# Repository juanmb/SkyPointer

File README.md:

# SkyPointer

## Description

An open-hardware altazimuth mount with a laser pointer.

The following block diagram shows the current setup:

## CAD

The SkyPointer mechanical parts were designed to be easily fabricated with a 3D
printer. The `cad` folder contains the CAD files in Step, STL and
[FreeCAD](http://www.freecadweb.org) formats.

## Electronics

Circuit schematics and PCB layout were designed with [Kicad](http://kicad.org).
They are stored in the `kicad` folder.

## Arduino

An Arduino Uno board controls two stepper motors (azimuth and elevation) using
a [CNC shield](http://blog.protoneer.co.nz/arduino-cnc-shield/) with some
modifications (documentation in progress).

The Arduino firmware is located in a
[separate repo](https://github.com/davidvg/ArduinoSkyPointer).

## The Python server

The server receives "goto" messages from
[Stellarium](http://www.stellarium.org/) and sends "current position" packets back.

The Stellarium client-server protocol is documented
[here](http://www.stellarium.org/wiki/index.php/Telescope_Control_%28client-server%29).

### Installing the server in GNU/Linux

Install the required dependencies using your package manager. In Debian/Ubuntu,
you can use apt-get like this

```
$ sudo apt-get install pyqt4-dev-tools python-numpy python-scipy
```

Now you can install the *skypointer* package with pip

```
$ sudo pip install skypointer
```

Alternatively, you can clone this repo and call `setup.py` directly from the
`python` folder

```
$ git clone https://github.com/juanmb/SkyPointer.git
$ cd python
$ python setup.py install
```

For development, it is strongly recommended to install this package into a
[virtual environment](https://virtualenv.pypa.io/en/latest/).

### Installing the server in Windows

Using [Anaconda](https://www.continuum.io/downloads):

```
conda install numpy scipy pyserial pyqt
```

Now you can install the skypointer package using pip

```
$ pip install skypointer
```

### Usage

Run `skypointer-gui`.

### Communication with Stellarium

* Start `skypointer-gui`.

* Check *Enable server* in the *Configuration* tab, select a server port number
  and click *Apply*.

* Start Stellarium.

* Enable the plugin *Telescope control* in Stellarium. If it was disabled,
  you will need to restart Stellarium (only the first time).

* In the configuration window of the *Telescope control* plugin, add a new
  telescope and select the option "External software or a remote computer".

* Choose a name and select "Equinox of the date (JNow)".

* Enter the TCP port of the server.

* Close the dialog and press "Connect".

Now you can send the equatorial coordinates of the selected object in
Stellarium to the *SkyPointer* server by pressing `Ctrl+1`.

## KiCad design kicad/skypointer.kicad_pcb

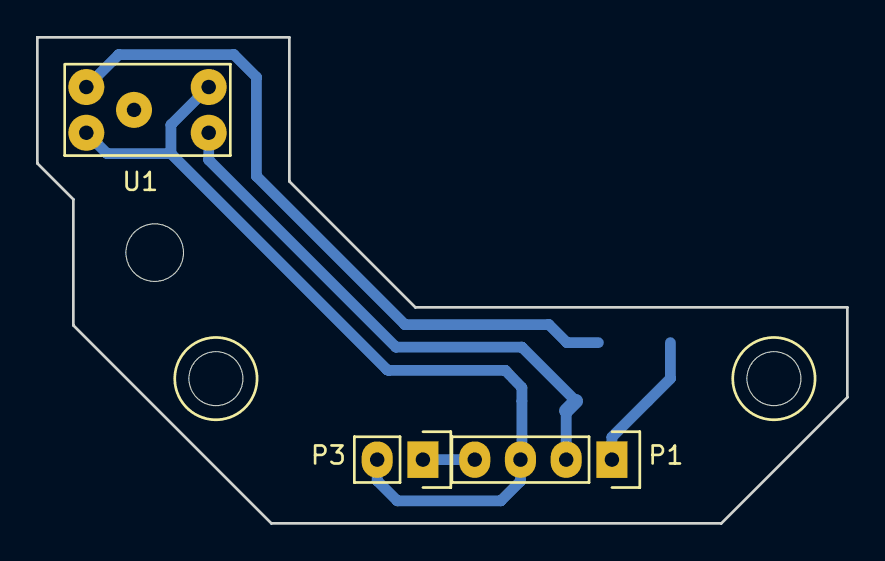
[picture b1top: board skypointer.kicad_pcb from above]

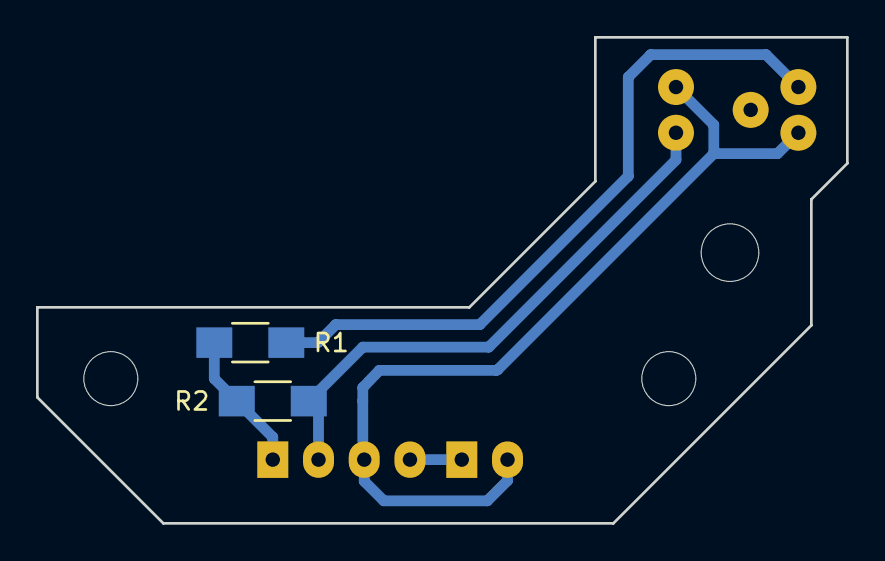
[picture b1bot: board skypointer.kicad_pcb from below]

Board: 2 copper layers, 45.0 x 27.0 mm, 5 parts (2 on the bottom side), 5 nets.

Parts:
P1: CONN_01X04; Pin_Header_Straight_1x04
P3: Laser; Pin_Header_Straight_1x02
R1: 220; R_1206_HandSoldering
R2: 10k; R_1206_HandSoldering
U1: TCST1230

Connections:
+5V: P1.1, R1.1, R2.1
GND: P1.3, P3.2, U1.2, U1.4
unnamed: P1.2, R2.2, U1.3
unnamed: P1.4, P3.1
unnamed: R1.2, U1.1

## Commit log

2015-04-20 Import some files
2015-05-08 Fix two (copy-paste) bugs. Add some info to README.md
2015-05-24 Implement Taki's telescope pointing model
2015-08-05 Improve PointingModel API. Don't use pyephem
2015-08-30 gamepad.py: step movement working
2015-09-02 Fix gamepad.py script
2015-09-08 Split code in files. Add Gamepad class.
2015-09-19 Read hardware ID. Fix some bugs
2015-10-04 Improve the pointing model. Add script for calculating mount errors
2015-10-08 Fix some stupid bugs. Increase verbosity of log messages
2015-10-11 Read options from a configuration file
2015-11-07 Retry and flush the buffer when a serial cmd fails
2015-11-07 Calculate pointing errors reading observations from a file
2016-01-06 Add CAD files
2016-01-10 File arduino/skypointer.ino added. It includes the Arduino code for the SkyPointer.
2016-01-12 Adjust dimensions in CAD files
2016-01-18 Add Kicad files
2016-02-28 Read and write calibration values to EEPROM
2016-03-06 Add a MOSFET to the PCB
2016-03-06 Start new package 'sp_controller' (QT GUI)
2016-03-09 Modify some mechanical dimensions. Add Arduino enclosure
2016-03-12 Update mechanical parts
2016-03-28 Work on sp_controller
2016-03-28 Fix pcb dimensions
2016-04-03 Work on UI
2016-04-03 Reorder files. Move Python package to a subfolder
2016-04-03 Add skypointer_motorshield Arduino library
2016-04-03 Update README (work in progress)
2016-04-04 Remove MOSFET from PCB
2016-04-05 Makefile added to /arduino and .gitignore updated to ignore Arduino's build directory.
2016-04-05 Add Stellarium server to GUI. Many other changes
2016-04-07 Ignore events from arrow keys if the pointer is unconnected
2016-04-09 Different pins for N and P-channel Mosfets. Makefile updated. gitignore updated with .swp files.
2016-04-09 Fix installation error. Send the current position back to Stellarium
2016-04-09 Clean up some code with decorator 'requires_pointer'
2016-04-10 Update CAD models
2016-04-14 Function SkyPointer_MotorShieild::laser() turns the laser on and off, setting the appropiate pin depending on the type of MOSFET. Comments cleanup.
2016-04-18 Minor code corrections.
2016-12-14 Fix a compatibility issue with QT library
2016-12-15 Remove Arduino firmware. Update README
2016-12-15 Fix block diagram
2020-12-08 Add example script star_walk.py
2021-11-08 Update README.md
    https://forum.kicad.info/t/warning-avoid-all-links-to-kicad-pcb-org-use-kicad-org/31521
